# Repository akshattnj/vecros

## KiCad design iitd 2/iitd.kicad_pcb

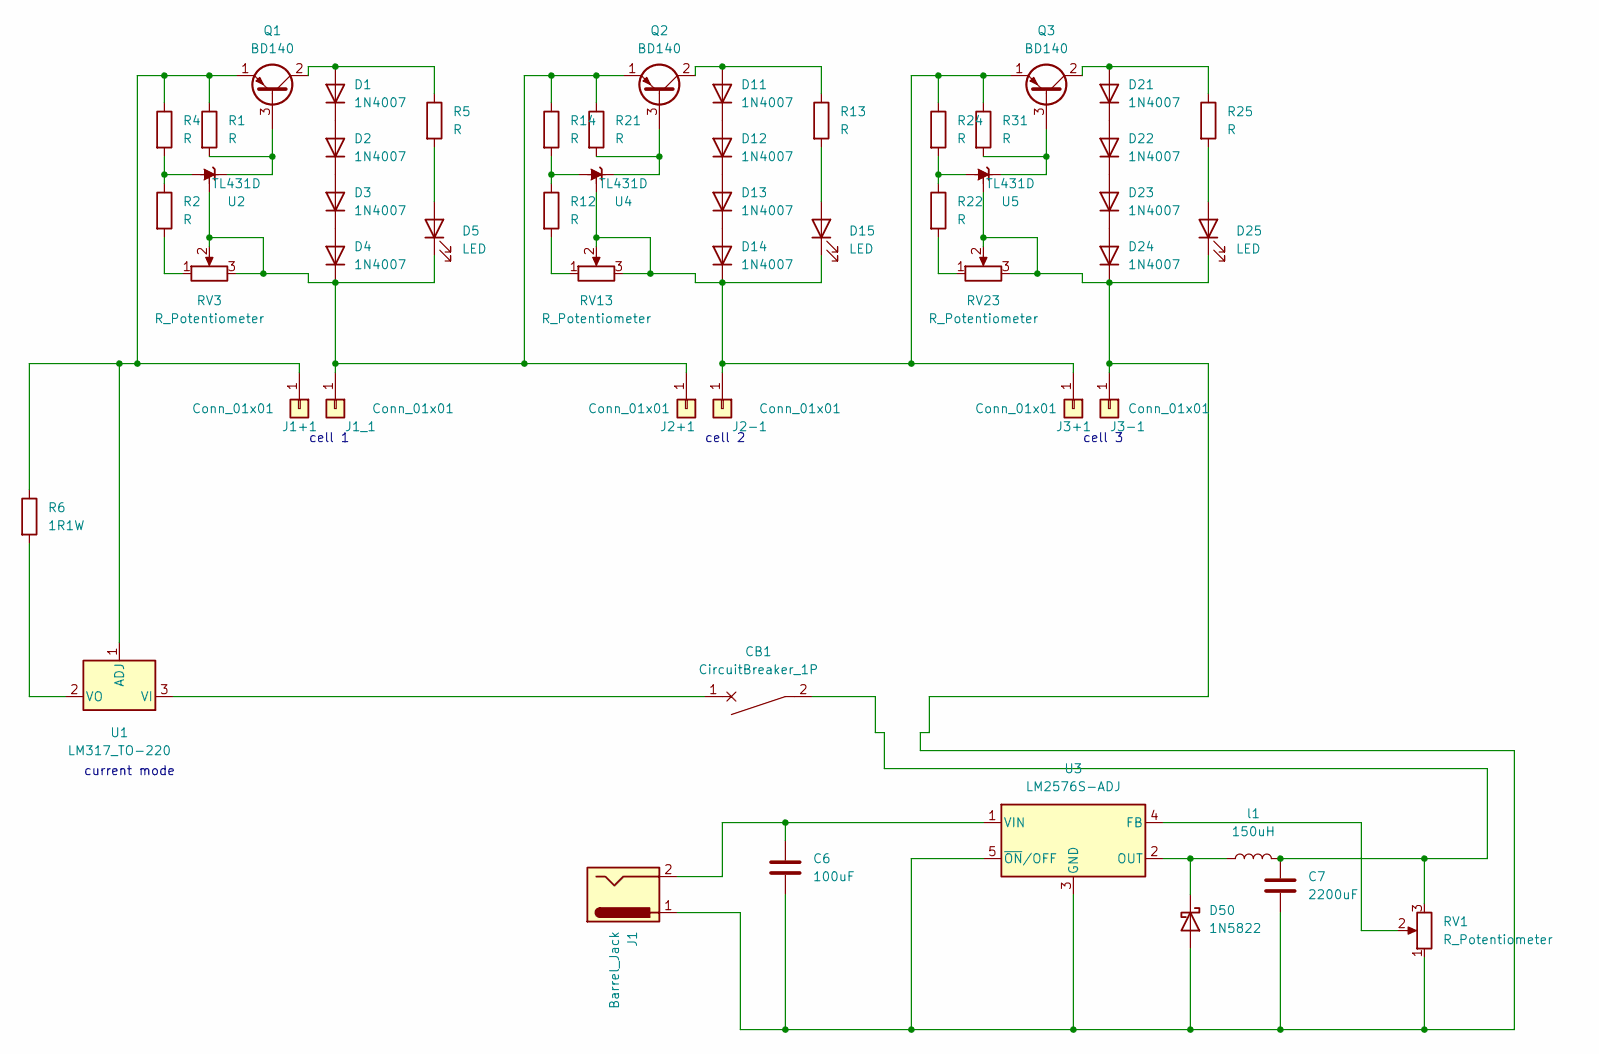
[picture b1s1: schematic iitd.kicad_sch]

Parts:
C6: 100uF; CP_Radial_D4.0mm_P2.00mm
C7: 2200uF; CP_Radial_D4.0mm_P2.00mm
CB1: CircuitBreaker_1P; SW_Tactile_Straight_KSL0Axx1LFTR
D1, D2, D3, D4, D11, D12, D13, D14, D21, D22, D23, D24: 1N4007; D_DO-41_SOD81_P10.16mm_Horizontal
D5, D15, D25: LED; D_5W_P10.16mm_Horizontal
D50: 1N5822; D_DO-201AD_P15.24mm_Horizontal
J1: Barrel_Jack; BarrelJack_CUI_PJ-063AH_Horizontal_CircularHoles
J1+1, J1_1, J2+1, J2-1, J3+1, J3-1: Conn_01x01; PinHeader_1x01_P1.00mm_Horizontal
Q1, Q2, Q3: BD140; TO-126-3_Vertical
R1, R4, R21: R; R_Axial_DIN0309_L9.0mm_D3.2mm_P15.24mm_Horizontal
R2, R5, R12, R13, R14, R22, R24, R25, R31: R; R_Axial_DIN0309_L9.0mm_D3.2mm_P12.70mm_Horizontal
R6: 1R1W; R_Axial_DIN0309_L9.0mm_D3.2mm_P12.70mm_Horizontal
RV1, RV3, RV13, RV23: R_Potentiometer; Potentiometer_ACP_CA14-H2,5_Horizontal
U1: LM317_TO-220; TO-220-3_Vertical
U2, U4, U5: TL431D; SOIC-8_3.9x4.9mm_P1.27mm
U3: LM2576S-ADJ; TO-263-5_TabPin3
l1: 150uH; L_Axial_L6.6mm_D2.7mm_P2.54mm_Vertical_Vishay_IM-2

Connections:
unnamed: C7.1, CB1.2, RV1.3, l1.2
unnamed: D1.1 (K), D2.2 (A)
unnamed: D1.2 (A), Q1.2 (C), R5.1
unnamed: D2.1 (K), D3.2 (A)
unnamed: D3.1 (K), D4.2 (A)
unnamed: D4.1 (K), D5.1 (K), J1_1.1, J2+1.1, Q2.1 (E), R14.1, R21.1, RV3.2, RV3.3, U2.8 (REF)
unnamed: D5.2 (A), R5.2
unnamed: D11.1 (K), D12.2 (A)
unnamed: D11.2 (A), Q2.2 (C), R13.1
unnamed: D12.1 (K), D13.2 (A)
unnamed: D13.1 (K), D14.2 (A)
unnamed: D14.1 (K), D15.1 (K), J2-1.1, J3+1.1, Q3.1 (E), R24.1, R31.1, RV13.2, RV13.3, U4.8 (REF)
unnamed: D15.2 (A), R13.2
unnamed: D21.1 (K), D22.2 (A)
unnamed: D21.2 (A), Q3.2 (C), R25.1
unnamed: D22.1 (K), D23.2 (A)
unnamed: D23.1 (K), D24.2 (A)
unnamed: C6.1, C7.2, D24.1 (K), D25.1 (K), D50.2 (A), J1.1, J3-1.1, RV1.1, RV23.2, RV23.3, U3.3 (GND), U3.5 (~ON/OFF), U5.8 (REF)
unnamed: D25.2 (A), R25.2
unnamed: D50.1 (K), U3.2 (OUT), l1.1
unnamed: J1+1.1, Q1.1 (E), R1.1, R4.1, R6.1, U1.1 (ADJ)
unnamed: C6.2, J1.2, U3.1 (VIN)
unnamed: Q1.3 (B), R1.2, U2.1 (K)
unnamed: Q2.3 (B), R21.2, U4.1 (K)
unnamed: Q3.3 (B), R31.2, U5.1 (K)
unnamed: R2.1, R4.2, U2.2 (A), U2.3 (A), U2.6 (A), U2.7 (A)
unnamed: R2.2, RV3.1
unnamed: R6.2, U1.2 (VO)
unnamed: R12.1, R14.2, U4.2 (A), U4.3 (A), U4.6 (A), U4.7 (A)
unnamed: R12.2, RV13.1
unnamed: R22.1, R24.2, U5.2 (A), U5.3 (A), U5.6 (A), U5.7 (A)
unnamed: R22.2, RV23.1
unnamed: RV1.2, U3.4 (FB)
unnamed: CB1.1, U1.3 (VI)

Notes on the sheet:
cell 2
current mode
cell 3
cell 1

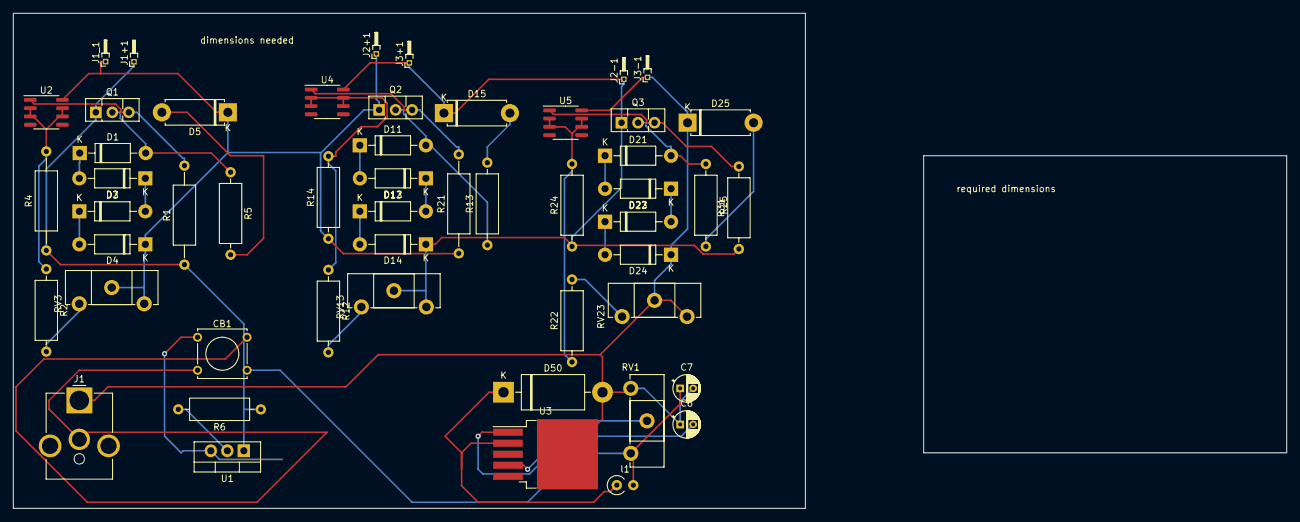
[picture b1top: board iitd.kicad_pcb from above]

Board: 2 copper layers, 121.9 x 76.2 mm, 52 parts (0 on the bottom side), 34 nets.

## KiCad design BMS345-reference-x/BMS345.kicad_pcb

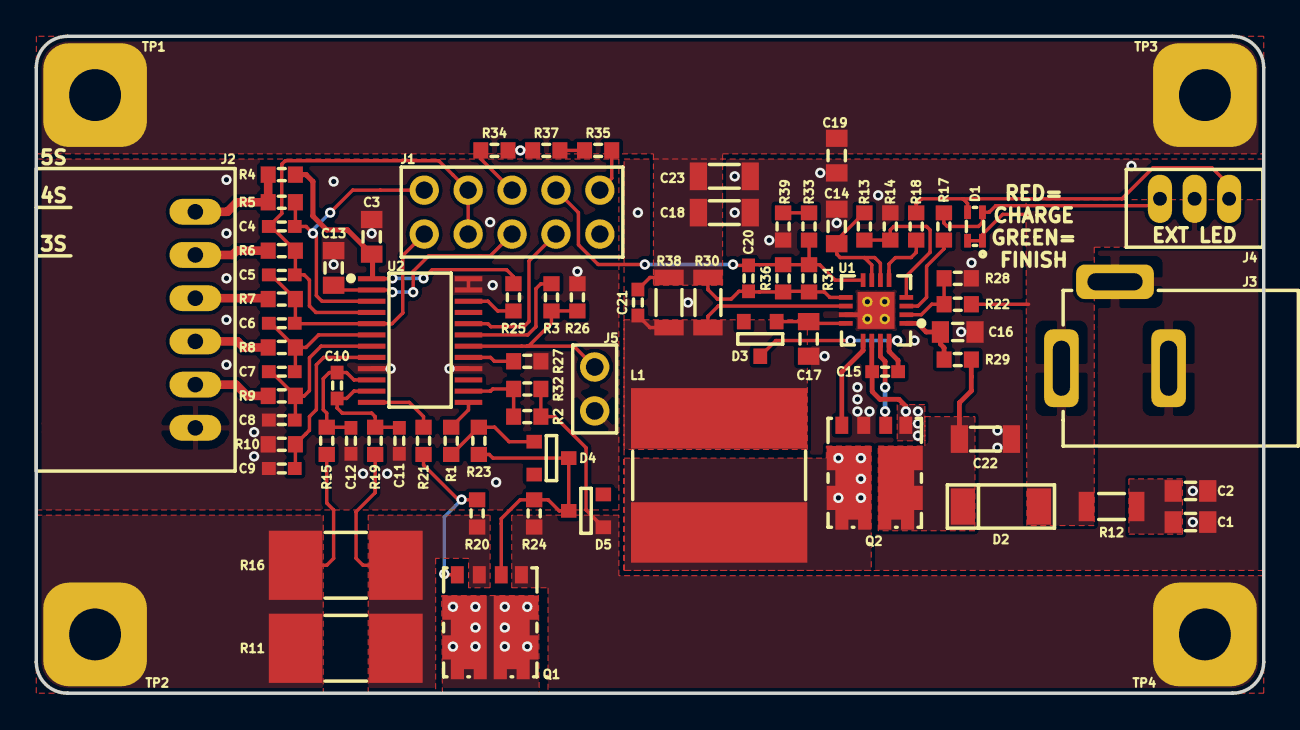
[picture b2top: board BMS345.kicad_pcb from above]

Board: 2 copper layers, 71.0 x 38.0 mm, 81 parts (0 on the bottom side), 54 nets.

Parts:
C1, C2, C3, C13, C14, C16, C17, C19: 1u; C0805
C4, C5, C6, C7, C8, C9, C10, C11, C12, C15, C21: 100n; C0603
C18, C22, C23: 10u; C1206
C20: 18p; C0603
D1: RED/GREEN; KingBright_KPTB
D2: Schottky; SOD-128
D3, D4: Schottky; SOT-23Z
D5: 10V; SOT-23Z
J1: CONFIG; PinHeader_2x05_P2.54mm_Vertical
J2: BATT; JSTXH_S6B
J3: DC Jack; DC_Jack
J4: EXTLED; JSTPH_3P
J5: NTC; 2P_2.54mm_header
L1: 10u; SRN1060
Q1, Q2: NMOS; SO8FLDual
R1, R3, R17, R18, R21, R25, R26: 10k; R0603
R2, R20, R22, R23, R31, R32: 1M; R0603
R4, R5, R6, R7, R8, R9, R10: 1K; R0603
R11, R16: 8m; R2512SNS
R12: 2R; R1206
R13, R14: 10K; R0603
R15, R19: 100R; R0603
R24: 3M3; R0603
R27, R33, R39: 100k; R0603
R28: 75K; R0603
R29: 10R; R0603
R30, R38: 39m; R1206
R34, R35, R37: 249k; R0603
R36: 33M; R0603
TP1: BATT+; Pad_6mm
TP2: BATT-; Pad_6mm
TP3: PACK+; Pad_6mm
TP4: PACK-; Pad_6mm
U1: BQ24650; QFN16
U2: BQ77915; TSSOP-24

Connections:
+24V: D1.1, D1.3, D2.2, J3.1, J4.2, R12.2, R22.2
/AVDD: C13.1, J1.6, U2.2
/BATT-: R11.2, R15.1, R16.2, TP2.1
/CCFG: J1.4, U2.20
/PACK+: C18.1, C19.2, C20.1, C21.2, C23.1, R30.2, R31.2, R36.2, R38.2, TP1.1, TP3.1, U1.9
/TS: R13.1, R14.2, U1.4
/VC3: C5.2, C6.1, J1.10, R7.1, U2.5
/VC4: C4.2, C5.1, J1.7, J1.8, R6.1, U2.4
/VC5: C4.1, J1.9, R5.1, U2.3
/VFB: C20.2, J1.3, R31.1, R33.2, R36.1, U1.8
/VREF: C14.2, R13.2, U1.6, U1.7
GND: C3.2, C8.2, C9.1, C11.1, C12.2, C13.2, J1.2, J2.1, J5.2, R10.2, R26.1, R27.1, U2.9, U2.16, U2.23, U2.24
GNDPWR: C1.1, C2.1, C14.1, C16.2, C17.2, C18.2, C19.1, C22.2, C23.2, D5.2, J3.2, J3.3, Q1.5, Q2.2, R2.1, R14.1, R24.1, R28.1, R32.1, R34.2, R37.2, R39.1, TP4.1, U1.11, U1.17
unnamed: C1.2, C2.2, R12.1
unnamed: C3.1, R4.1, R25.1, U2.1
unnamed: C6.2, C7.1, R8.1, U2.6
unnamed: C7.2, C8.1, R9.1, U2.7
unnamed: C9.2, R10.1, U2.8
unnamed: C10.1, C11.2, R19.2, U2.11
unnamed: C10.2, C12.1, R15.2, U2.10
unnamed: C15.1, D3.1, U1.16
unnamed: C15.2, L1.1, Q2.4, Q2.5, U1.14
unnamed: C16.1, R29.1, U1.1
unnamed: C17.1, D3.2, U1.12
unnamed: C21.1, L1.2, R30.1, R38.1, U1.10
unnamed: C22.1, D2.1, Q2.6, R29.2
unnamed: D1.2, J4.3, R17.2
unnamed: D1.4, J4.1, R18.2
unnamed: D4.1, D5.1, Q1.1, R23.1, R24.2
unnamed: D4.2, R1.1, R23.2
unnamed: J1.1, R35.1
unnamed: J1.5, R34.1
unnamed: J2.2, R9.2
unnamed: J2.3, R8.2
unnamed: J2.4, R7.2
unnamed: J2.5, R6.2
unnamed: J2.6, R4.2, R5.2
unnamed: J5.1, R3.1, R26.2, U2.18
unnamed: Q1.2, R11.1, R16.1, R19.1, R20.1
unnamed: Q1.3, R20.2, R21.1
unnamed: Q1.4, Q1.6
unnamed: Q2.1, U1.15
unnamed: Q2.3, U1.13
unnamed: R1.2, U2.13
unnamed: R2.2, R32.2, U2.14
unnamed: R3.2, U2.19
unnamed: R17.1, U1.3
unnamed: R18.1, U1.5
unnamed: R21.2, U2.12
unnamed: R22.1, R28.2, U1.2
unnamed: R25.2, U2.22
unnamed: R27.2, U2.17
unnamed: R33.1, R39.2
unnamed: R35.2, R37.1

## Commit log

2023-02-01 second
